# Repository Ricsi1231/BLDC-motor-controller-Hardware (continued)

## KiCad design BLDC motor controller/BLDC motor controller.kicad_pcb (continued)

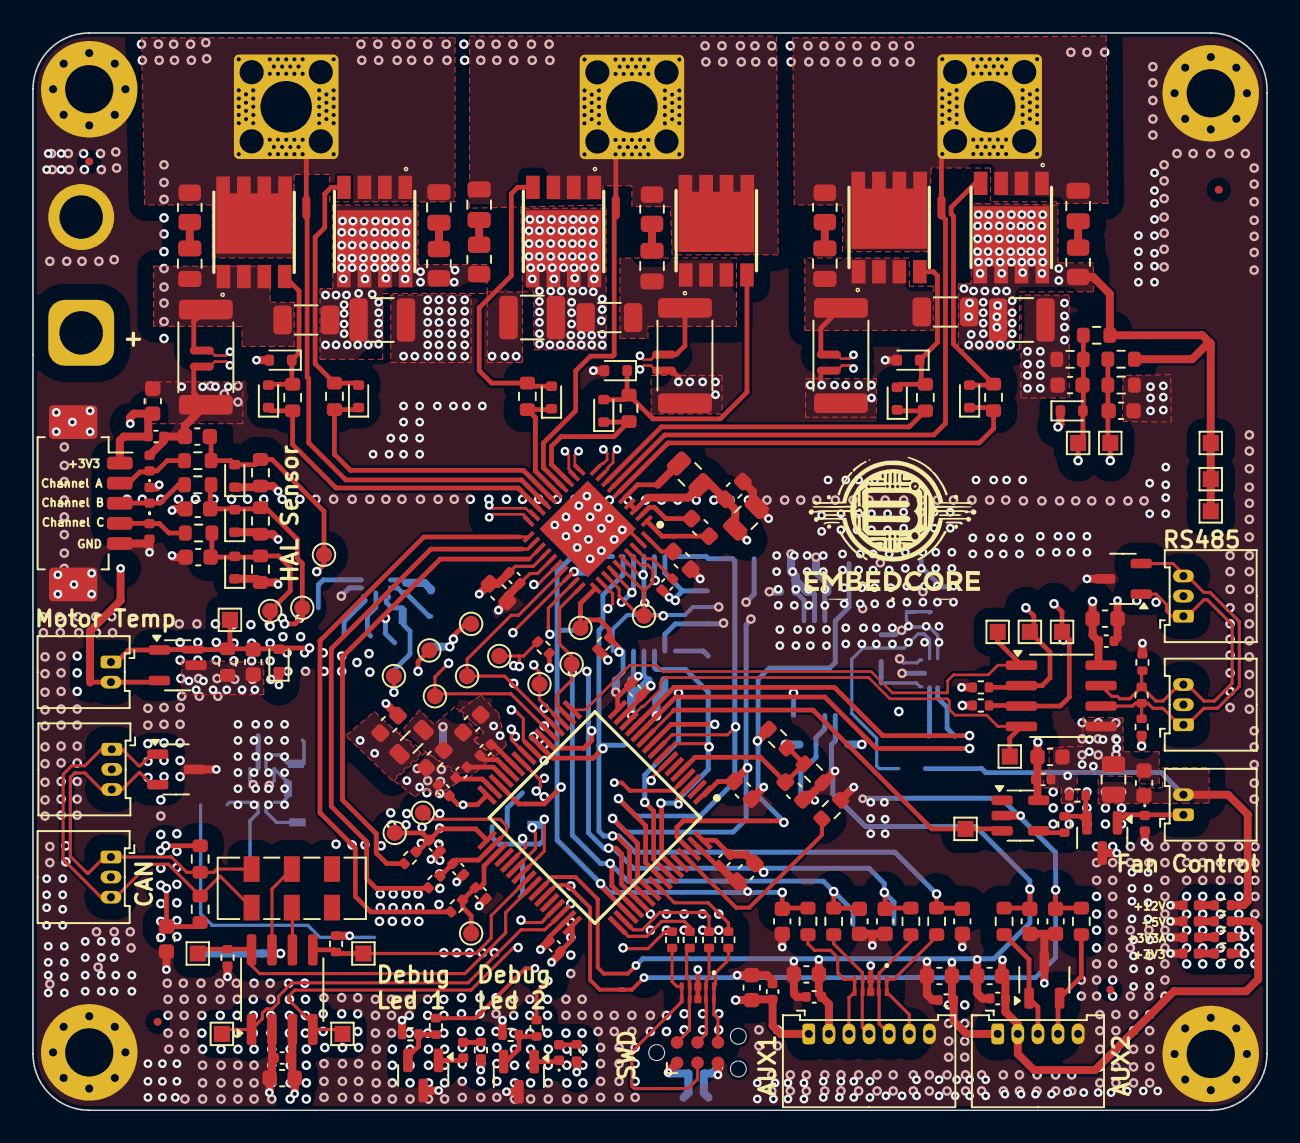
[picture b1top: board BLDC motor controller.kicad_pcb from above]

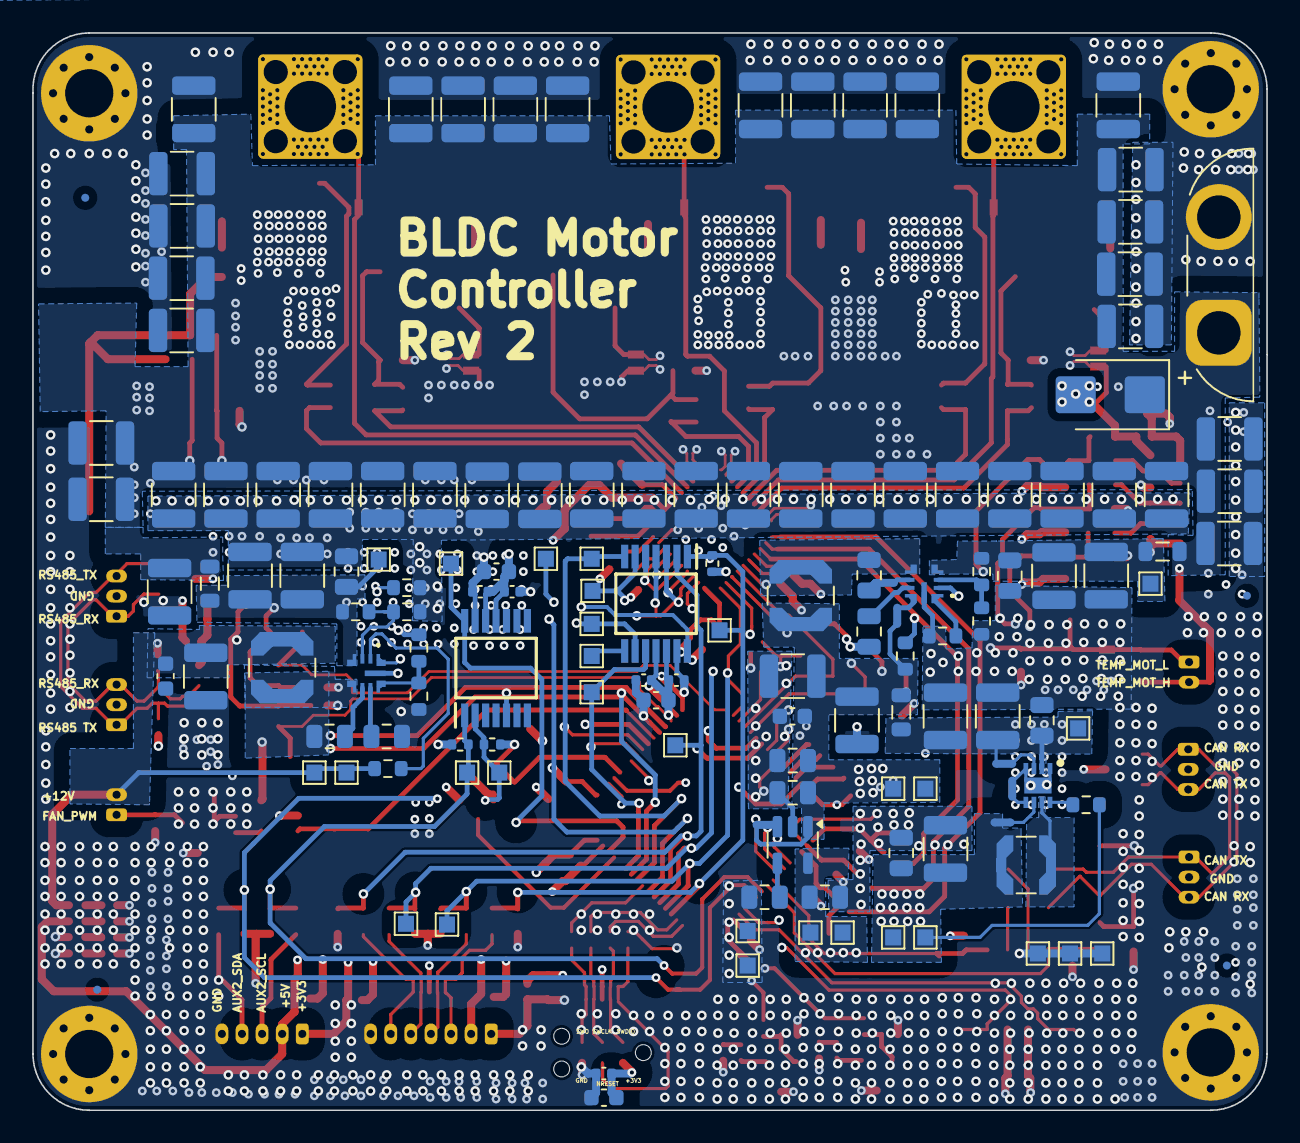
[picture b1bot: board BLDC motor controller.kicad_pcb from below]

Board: 6 copper layers, 76.8 x 67.0 mm, 382 parts (142 on the bottom side), 156 nets.

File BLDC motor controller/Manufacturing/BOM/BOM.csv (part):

Reference,Value,Datasheet,Footprint,Qty,DNP,Manufacturer,Manufacturer Part Number,Distributer Link
"C501,C502,C503,C504,C505,C506,C507,C508,C509,C510,C511,C512,C513,C514,C515,C516,C517,C518,C519,C520,C521,C522,C523,C524,C525,C526,C527,C528,C529,C530,C531,C532,C533,C534,C535,C536,C537,C538,C539,C540,C541,C542,C1104,C1204,C1305",10u 100V X7R,https://product.tdk.com/system/files/dam/doc/product/capacit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,Capacitor_SMD:C_1210_3225Metric,45,,TDK,C3225X7R2A106K250AC ,https://eu.mouser.com/
"C601,C602,C603,C609,C610,C611,C617,C618",2u2 100V X7R,https://eu.mouser.com/datasheet/2/447/KEM_C1023_X7R_AUTO_SMD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,Capacitor_SMD:C_1210_3225Metric,8,,KEMET,C1210C225J1RACAUTO,https://eu.mouser.com/ 
"C604,C606,C612,C614,C620",100n 100V X7R,https://eu.mouser.com/datasheet/2/40/X7RDielectric-2943470.pdf,Capacitor_SMD:C_0805_2012Metric,5,,KYOCERA AVX,08051C104JAZ2A,https://eu.mouser.com/  
"C605,C613",1u 50V X7R,https://eu.mouser.com/datasheet/2/40/KGM_X7R-3223212.pdf,Capacitor_SMD:C_0805_2012Metric,2,,KYOCERA AVX,08055C105JAT2A,https://eu.mouser.com/   
"C607,C615",22u 25V X7R,https://eu.mouser.com/datasheet/2/396/Tayio_Yuden_1102023_MS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,Capacitor_SMD:C_1210_3225Metric,2,,TAIYO YUDEN,MSAST32MSB7226KPNB25,https://eu.mouser.com/   
"C608,C616",100n 25V X7R,https://eu.mouser.com/datasheet/2/447/KEM_C1090_X7R_ESD-3316292.pdf,Capacitor_SMD:C_0603_1608Metric,2,,KEMET,C0603C104J3RECAUTO7411,https://eu.mouser.com/    
C619,10u 25V X7R,https://eu.mouser.com/datasheet/2/281/1/GRM32DR71E106KA12_01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,Capacitor_SMD:C_1210_3225Metric,1,,Murata Electronics,GRM32DR71E106KA12K,https://eu.mouser.com/    
C622,22u 16V X7R,https://eu.mouser.com/datasheet/2/396/Tayio_Yuden_1102023_MS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,Capacitor_SMD:C_1210_3225Metric,1,,TAIYO YUDEN,MSAST32MSB7226KPNB25,https://eu.mouser.com/     
"C623,C702,C703",100n 25V X7R,https://eu.mouser.com/datasheet/2/40/X7RDielectric-2943470.pdf,Capacitor_SMD:C_0805_2012Metric,3,,KYOCERA AVX,08053C104KAZ2A,https://eu.mouser.com/      
C701,2u2 16V X7R,https://eu.mouser.com/datasheet/2/447/KEM_C1023_X7R_AUTO_SMD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,Capacitor_SMD:C_0805_2012Metric,1,,KEMET,C0805C225K4RAC3123,https://eu.mouser.com/      
C704,4u7 16V X7R,https://eu.mouser.com/datasheet/2/447/KEM_C1002_X7R_SMD-3316098.pdf,Capacitor_SMD:C_0805_2012Metric,1,,KEMET,C0805C475K4RAC7210,https://eu.mouser.com/       
C801,1u 16V X7R,https://eu.mouser.com/datasheet/2/396/mlcc06_hq_AUTO_e-1901145.pdf,Capacitor_SMD:C_0603_1608Metric,1,,TAIYO YUDEN,EMK107B7105KA8T,https://eu.mouser.com/       
"C802,C807,C808,C810,C1007,C1601,C1604,C1701,C1703,C1801,C1901,C2001,C2003,C2009,C2011,C2015,C2024",4u7 16V X7R,https://eu.mouser.com/datasheet/2/281/1/GRM188Z71C475KE21_01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,Capacitor_SMD:C_0603_1608Metric,17,,Murata Electronics,GRM188Z71C475KE21D,https://eu.mouser.com/       
"C803,C804,C805,C806,C809,C811,C1008,C1602,C1603,C1605,C1606,C1702,C1802,C1902,C2002,C2004,C2010,C2012,C2016,C2022",100n 16V X7R,https://product.tdk.com/system/files/dam/doc/product/capacit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,Capacitor_SMD:C_0402_1005Metric,20,,TDK,C1005X7R1C104K050BC,https://eu.mouser.com/       
"C1001,C2017",2u2 100V X7R,https://product.tdk.com/system/files/dam/doc/product/capacit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,Capacitor_SMD:C_0805_2012Metric,2,,TDK,CGA4J1X7R2A225K125AC,https://eu.mouser.com/        
"C1002,C1006,C1401,C1402,C1501,C2018,C2201",100n 100V X7R,https://eu.mouser.com/datasheet/2/40/AutoMLCCKAF-3218225.pdf,Capacitor_SMD:C_0603_1608Metric,7,,KYOCERA AVX,KAF15BR72A104KT,https://eu.mouser.com/        
C1005,1u 100V X7R,https://eu.mouser.com/datasheet/2/40/AutoMLCC-2952695.pdf,Capacitor_SMD:C_0805_2012Metric,1,,KYOCERA AVX,08051C105K4T2A,https://eu.mouser.com/         
C1009,1u 6V3 X5R,https://eu.mouser.com/datasheet/2/585/Samsung_MLCC_1837944-1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,Capacitor_SMD:C_0402_1005Metric,1,,Samsung Electro-Mechanics,CL05B105KQ5QNWC ,https://eu.mouser.com/          
C1010,1u 16V X5R,https://eu.mouser.com/datasheet/2/396/mlcc06_hq_AUTO_e-1901145.pdf,Capacitor_SMD:C_0603_1608Metric,1,,TAIYO YUDEN,EMK107B7105KA8T,https://eu.mouser.com/           
"C1011,C1012,C1013",1n 16V X7R,https://eu.mouser.com/datasheet/2/281/1/GRM155R71C103KA01_01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,Capacitor_SMD:C_0402_1005Metric,3,,Murata Electronics,GRM155R71C103KA01J,https://eu.mouser.com/            
"C1101,C1102,C1201,C1202,C1301,C1302",22n 100V X7R,https://eu.mouser.com/datasheet/2/40/AutoMLCCKAM-3216307.pdf,Capacitor_SMD:C_0805_2012Metric,6,,KYOCERA AVX,KAM21BR72A223KM,https://eu.mouser.com/             
"C1103,C1203,C1304",100n 100V X7R,https://www.we-online.com/components/products/datasheet/8853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,Capacitor_SMD:C_1206_3216Metric,3,,Wurth Elektronik,885382208006,https://eu.mouser.com/            
D401,SMBJ51CA-E3/52,https://www.vishay.com/docs/88392/smbj.pdf,Diode_SMD:D_SMB,1,,Vishay General Semiconductor,SMBJ51CA-E3/52,https://eu.mouser.com/            
"D1101,D1102,D1103,D1201,D1202,D1203,D1301,D1302,D1303,D1401,D1402,D1403,D1404,D1405",BAT41KFILM,https://eu.mouser.com/datasheet/2/389/bat41-1848934.pdf,Diode_SMD:D_SOD-523,14,,STMicroelectronics,BAT41KFILM,https://eu.mouser.com/            
"D2001,D2004",ESDR0524SMUTAG,https://www.st.com/resource/en/datasheet/esda5v3sc6.pdf,ESDR0524SMUTAG:ESDR0524SMUTAG,2,,onsemi,ESDR0524SMUTAG,https://eu.mouser.com/             
"D2002,D2003,D2005,D2006","DF3A5.6LFU,LF",https://www.st.com/resource/en/datasheet/esdal.pdf,Package_TO_SOT_SMD:SOT-23-3,4,,Toshiba,"DF3A5.6LFU,LF ",https://eu.mouser.com/              
D2007,CG0402MLC-3.3LG,https://eu.mouser.com/datasheet/2/54/MLC-777442.pdf,Diode_SMD:D_0402_1005Metric,1,,Bourns,CG0402MLC-3.3LG ,https://eu.mouser.com/              
"D2009,D2010,D2011",CG0402MLC-12G,https://eu.mouser.com/datasheet/2/54/MLC-777442.pdf,Diode_SMD:D_0402_1005Metric,3,,Bourns,CG0402MLC-12LG ,https://eu.mouser.com/              
"D2101,D2103",GREEN,https://eu.mouser.com/datasheet/2/917/stanley_led_2018_02-15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,LED_SMD:LED_0402_1005Metric,2,,Stanley Electric,FHD1105P-TR ,https://eu.mouser.com/            
D2102,RED,https://eu.mouser.com/datasheet/2/917/downloaddatafile-3318113.pdf,LED_SMD:LED_0402_1005Metric,1,,Stanley Electric,FHR1105P-TR ,https://eu.mouser.com/            
D2104,YELLOW,https://eu.mouser.com/datasheet/2/917/stanley_led_2018_02-15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,LED_SMD:LED_0402_1005Metric,1,,Stanley Electric,FHY1105P-TR ,https://eu.mouser.com/             
D2105,BLUE,https://www.we-online.com/components/products/datasheet/1500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,LED_SMD:LED_0402_1005Metric,1,,Wurth Elektronik,150040BS73220,https://eu.mouser.com/              
D2106,ORAGNGE,https://www.we-online.com/components/products/datasheet/1500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,LED_SMD:LED_0402_1005Metric,1,,Bivar,SM0402OC,https://eu.mouser.com/              
"F603,FB601,FB602,FB801",1k @100MHz,https://eu.mouser.com/datasheet/2/3/ACML-0805H-43744.pdf,Inductor_SMD:L_0805_2012Metric,4,,ABRACON,ACML-0805H-102-T ,https://eu.mouser.com/              
J2001,Conn_01x07,https://www.molex.com/en-us/products/part-detail/530480710?d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,Connector_Molex:Molex_PicoBlade_53048-0710_1x07_P1.25mm_Horizontal,1,,Molex,53048-0710 ,https://eu.mouser.com/              
"J2004,J2005,J2008,J2009",Conn_01x03,https://www.molex.com/en-us/products/part-detail/530480310?d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,Connector_Molex:Molex_PicoBlade_53048-0310_1x03_P1.25mm_Horizontal,4,,Molex,53048-0310,https://eu.mouser.com/              
"J2011,J2012",Conn_01x02,https://www.molex.com/en-us/products/part-detail/530480210?d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,Connector_Molex:Molex_PicoBlade_53048-0210_1x02_P1.25mm_Horizontal,2,,Molex,53048-0210,https://eu.mouser.com/              
J2202,Conn_01x05,https://www.molex.com/en-us/products/part-detail/530480510?d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,Connector_Molex:Molex_PicoBlade_53048-0510_1x05_P1.25mm_Horizontal,1,,Molex,53048-0510,https://eu.mouser.com/              
J2203,Conn_01x05,https://www.molex.com/en-us/products/part-detail/532610571?d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,Connector_Molex:Molex_PicoBlade_53261-0571_1x05-1MP_P1.25mm_Horizontal,1,,Molex,53261-0571,https://eu.mouser.com/              
"L601,L602",22.0u,https://eu.mouser.com/datasheet/2/597/lps4018-270702.pdf,inductor:L_Coilcraft_LPS4018,2,,Coilcraft,LPS4018-223MRC ,https://eu.mouser.com/              
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
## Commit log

2024-12-09 Added Rev 1 board
2025-03-05 Add REV 2 Board
